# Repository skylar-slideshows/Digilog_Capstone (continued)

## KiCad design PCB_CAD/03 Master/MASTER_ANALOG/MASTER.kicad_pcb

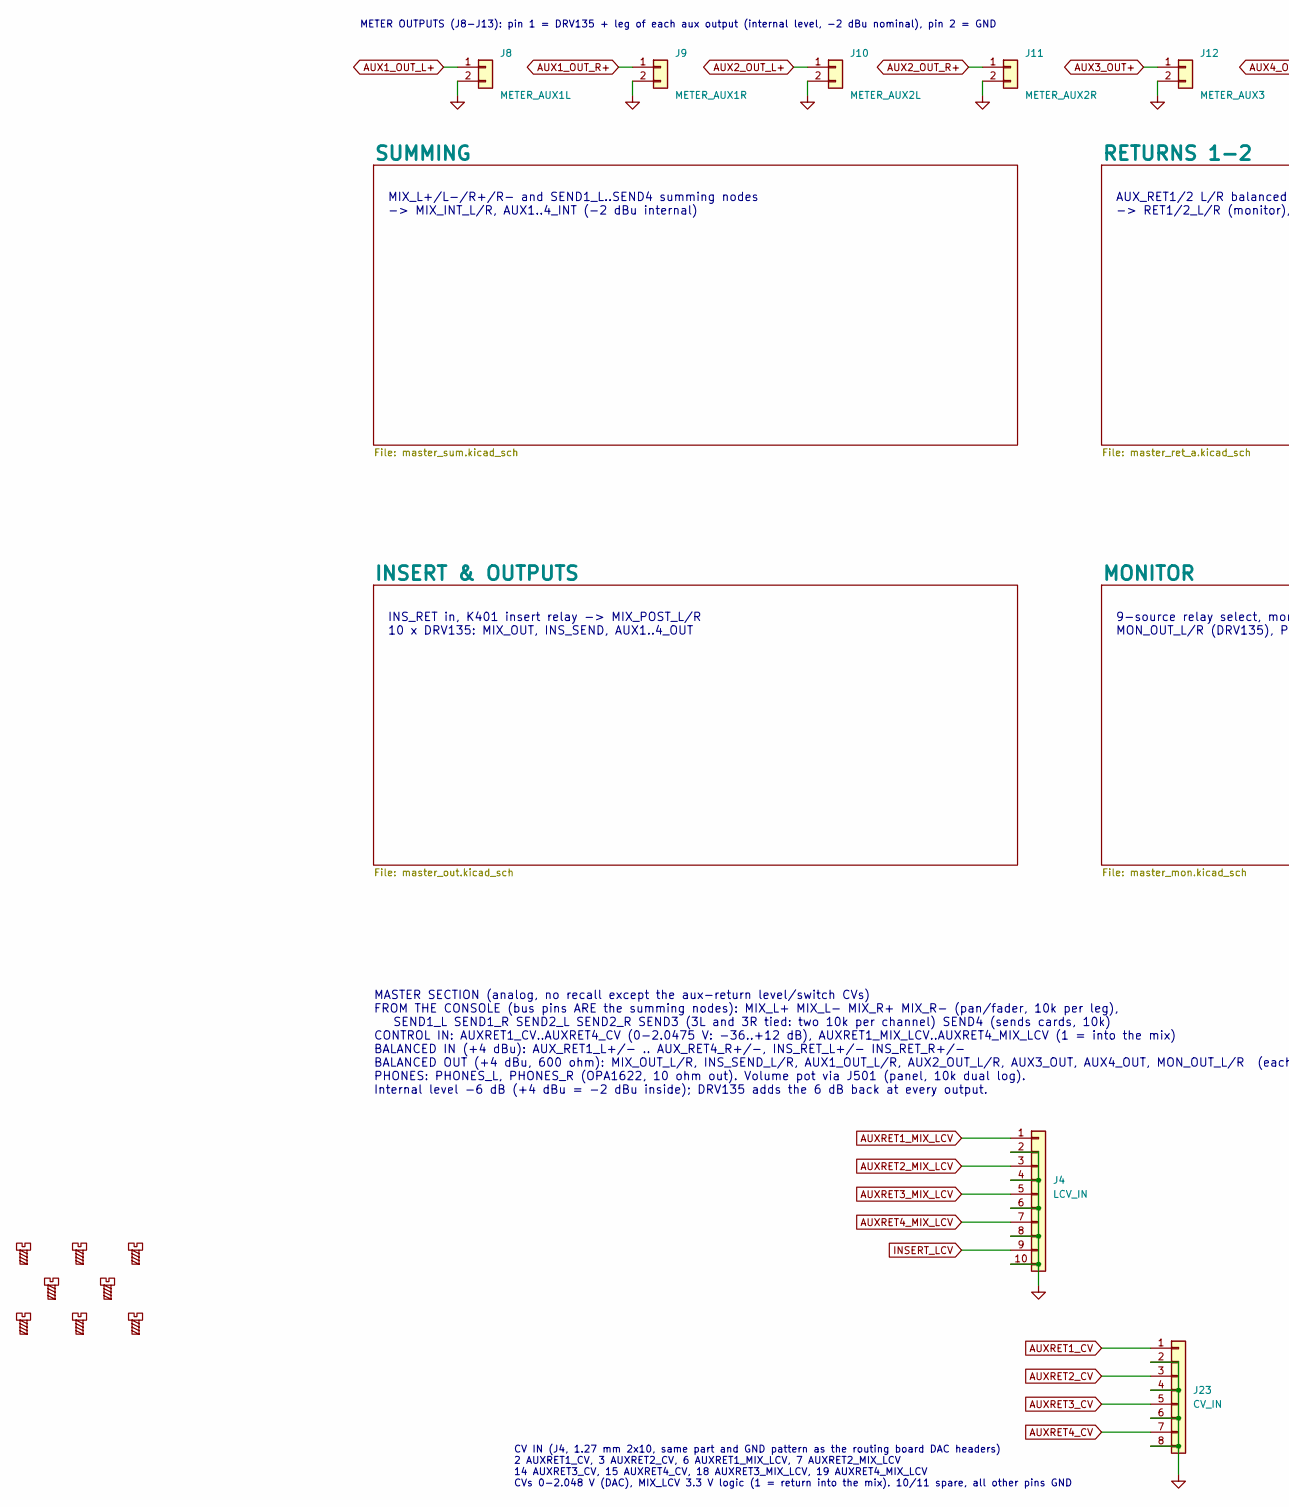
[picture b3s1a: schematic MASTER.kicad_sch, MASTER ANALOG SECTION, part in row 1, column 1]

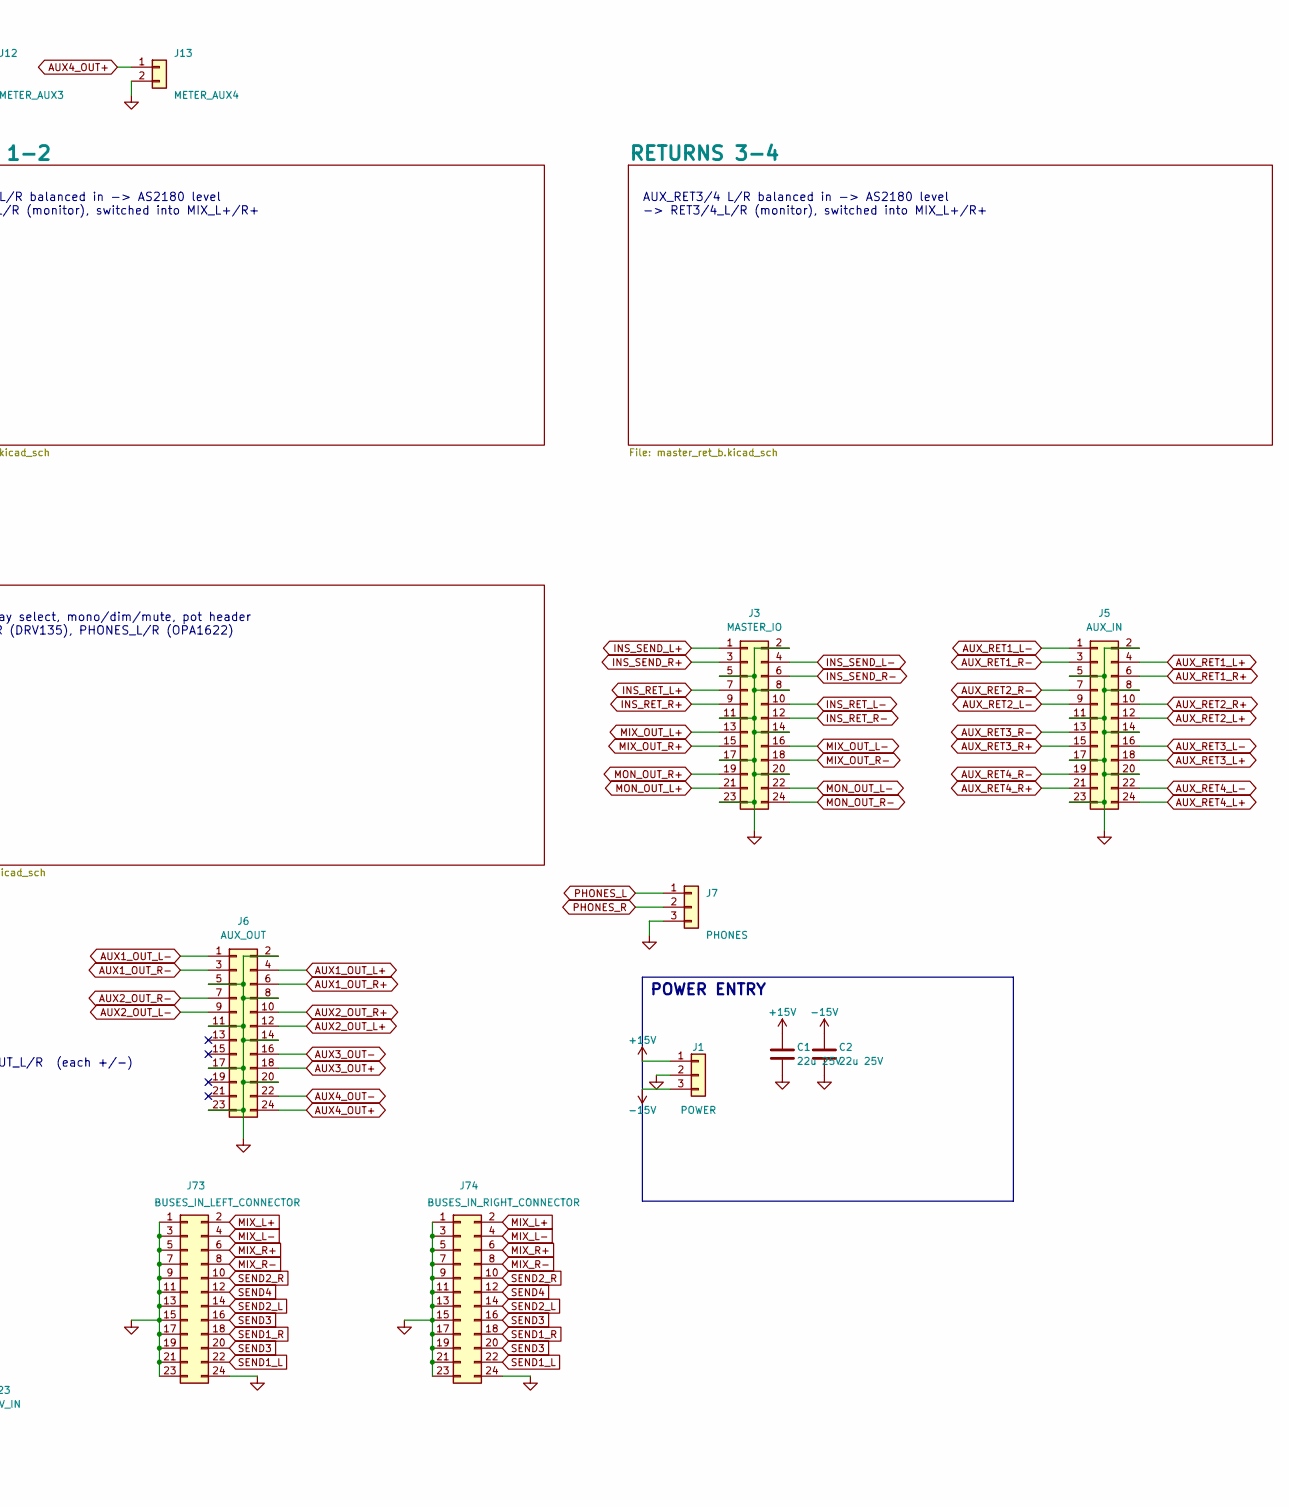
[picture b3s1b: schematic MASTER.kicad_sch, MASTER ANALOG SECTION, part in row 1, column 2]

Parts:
C1, C2: 22u 25V; C_1210_3225Metric; LCSC C21397
H1, H2, H3, H4, H5, H6, H7, H8: MountingScrew; MountingHole_3.2mm_M3; LCSC dnp
J1: POWER; Samtec_HPM-03-05-x-S_Straight_1x03_Pitch5.08mm; LCSC dnp
J3: MASTER_IO; IDC-Header_2x12_P2.54mm_Vertical; LCSC C53207829
J4: LCV_IN; PinHeader_1x10_P2.54mm_Vertical; LCSC dnp
J5: AUX_IN; IDC-Header_2x12_P2.54mm_Vertical; LCSC C53207829
J6: AUX_OUT; IDC-Header_2x12_P2.54mm_Vertical; LCSC C53207829
J7: PHONES; PinHeader_1x03_P2.54mm_Vertical; LCSC dnp
J8: METER_AUX1L; PinHeader_1x02_P2.54mm_Vertical; LCSC dnp
J9: METER_AUX1R; PinHeader_1x02_P2.54mm_Vertical; LCSC dnp
J10: METER_AUX2L; PinHeader_1x02_P2.54mm_Vertical; LCSC dnp
J11: METER_AUX2R; PinHeader_1x02_P2.54mm_Vertical; LCSC dnp
J12: METER_AUX3; PinHeader_1x02_P2.54mm_Vertical; LCSC dnp
J13: METER_AUX4; PinHeader_1x02_P2.54mm_Vertical; LCSC dnp
J23: CV_IN; PinHeader_1x08_P2.54mm_Vertical; LCSC dnp
J73: BUSES_IN_LEFT_CONNECTOR; IDC-Header_2x12_P2.54mm_Vertical; LCSC C53207829
J74: BUSES_IN_RIGHT_CONNECTOR; IDC-Header_2x12_P2.54mm_Vertical; LCSC C53207829

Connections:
+15V: C1.1, J1.1; also elsewhere on the board
-15V: C2.1, J1.3; also elsewhere on the board
AUX1_OUT_L+: J6.4, J8.1; also elsewhere on the board
AUX1_OUT_L-: J6.1; also elsewhere on the board
AUX1_OUT_R+: J6.6, J9.1; also elsewhere on the board
AUX1_OUT_R-: J6.3; also elsewhere on the board
AUX2_OUT_L+: J6.12, J10.1; also elsewhere on the board
AUX2_OUT_L-: J6.9; also elsewhere on the board
AUX2_OUT_R+: J6.10, J11.1; also elsewhere on the board
AUX2_OUT_R-: J6.7; also elsewhere on the board
AUX3_OUT+: J6.18, J12.1; also elsewhere on the board
AUX3_OUT-: J6.16; also elsewhere on the board
AUX4_OUT+: J6.24, J13.1; also elsewhere on the board
AUX4_OUT-: J6.22; also elsewhere on the board
AUXRET1_CV: J23.1; also elsewhere on the board
AUXRET1_MIX_LCV: J4.1; also elsewhere on the board
AUXRET2_CV: J23.3; also elsewhere on the board
AUXRET2_MIX_LCV: J4.3; also elsewhere on the board
AUXRET3_CV: J23.5; also elsewhere on the board
AUXRET3_MIX_LCV: J4.5; also elsewhere on the board
AUXRET4_CV: J23.7; also elsewhere on the board
AUXRET4_MIX_LCV: J4.7; also elsewhere on the board
AUX_RET1_L+: J5.4; also elsewhere on the board
AUX_RET1_L-: J5.1; also elsewhere on the board
AUX_RET1_R+: J5.6; also elsewhere on the board
AUX_RET1_R-: J5.3; also elsewhere on the board
AUX_RET2_L+: J5.12; also elsewhere on the board
AUX_RET2_L-: J5.9; also elsewhere on the board
AUX_RET2_R+: J5.10; also elsewhere on the board
AUX_RET2_R-: J5.7; also elsewhere on the board
AUX_RET3_L+: J5.18; also elsewhere on the board
AUX_RET3_L-: J5.16; also elsewhere on the board
AUX_RET3_R+: J5.15; also elsewhere on the board
AUX_RET3_R-: J5.13; also elsewhere on the board
AUX_RET4_L+: J5.24; also elsewhere on the board
AUX_RET4_L-: J5.22; also elsewhere on the board
AUX_RET4_R+: J5.21; also elsewhere on the board
AUX_RET4_R-: J5.19; also elsewhere on the board
GND: C1.2, C2.2, J1.2, J3.2, J3.5, J3.8, J3.11, J3.14, J3.17, J3.20, J3.23, J4.2, J4.4, J4.6, J4.8, J4.10, J5.2, J5.5, J5.8, J5.11, J5.14, J5.17, J5.20, J5.23, J6.2, J6.5, J6.8, J6.11, J6.14, J6.17, J6.20, J6.23, J7.3, J8.2, J9.2, J10.2, J11.2, J12.2, J13.2, J23.2, J23.4, J23.6, J23.8, J73.1, J73.3, J73.5, J73.7, J73.9, J73.11, J73.13, J73.15, J73.17, J73.19, J73.21, J73.23, J73.24, J74.1, J74.3, J74.5, J74.7, J74.9, J74.11, J74.13, J74.15, J74.17, J74.19, J74.21, J74.23, J74.24; also elsewhere on the board
INSERT_LCV: J4.9; also elsewhere on the board
INS_RET_L+: J3.7; also elsewhere on the board
INS_RET_L-: J3.10; also elsewhere on the board
INS_RET_R+: J3.9; also elsewhere on the board
INS_RET_R-: J3.12; also elsewhere on the board
INS_SEND_L+: J3.1; also elsewhere on the board
INS_SEND_L-: J3.4; also elsewhere on the board
INS_SEND_R+: J3.3; also elsewhere on the board
INS_SEND_R-: J3.6; also elsewhere on the board
MIX_L+: J73.2, J74.2; also elsewhere on the board
MIX_L-: J73.4, J74.4; also elsewhere on the board
MIX_OUT_L+: J3.13; also elsewhere on the board
MIX_OUT_L-: J3.16; also elsewhere on the board
MIX_OUT_R+: J3.15; also elsewhere on the board
MIX_OUT_R-: J3.18; also elsewhere on the board
MIX_R+: J73.6, J74.6; also elsewhere on the board
MIX_R-: J73.8, J74.8; also elsewhere on the board
MON_OUT_L+: J3.21; also elsewhere on the board
MON_OUT_L-: J3.22; also elsewhere on the board
MON_OUT_R+: J3.19; also elsewhere on the board
MON_OUT_R-: J3.24; also elsewhere on the board
PHONES_L: J7.1; also elsewhere on the board
PHONES_R: J7.2; also elsewhere on the board
SEND1_L: J73.22, J74.22; also elsewhere on the board
SEND1_R: J73.18, J74.18; also elsewhere on the board
SEND2_L: J73.14, J74.14; also elsewhere on the board
SEND2_R: J73.10, J74.10; also elsewhere on the board
SEND3: J73.16, J73.20, J74.16, J74.20; also elsewhere on the board
SEND4: J73.12, J74.12; also elsewhere on the board

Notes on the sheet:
MASTER SECTION (analog, no recall except the aux-return level/switch CVs) FROM THE CONSOLE (bus pins ARE the summing nodes): MIX_L+ MIX_L- MIX_R+ MIX_R- (pan/fader, 10k per leg), SEND1_L SEND1_R SEND2_L SEND2_R SEND3 (3L and 3R tied: two 10k per channel) SEND4 (sends cards, 10k) CONTROL IN: AUXRET1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
AUX_RET1/2 L/R balanced in -> AS2180 level -> RET1/2_L/R (monitor), switched into MIX_L+/R+
POWER ENTRY
CV IN (J4, 1.27 mm 2x10, same part and GND pattern as the routing board DAC headers) 2 AUXRET1_CV, 3 AUXRET2_CV, 6 AUXRET1_MIX_LCV, 7 AUXRET2_MIX_LCV 14 AUXRET3_CV, 15 AUXRET4_CV, 18 AUXRET3_MIX_LCV, 19 AUXRET4_MIX_LCV CVs 0-2.048 V (DAC), MIX_LCV 3.3 V logic (1 = return into the mix). 10/11 spare,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
9-source relay select, mono/dim/mute, pot header MON_OUT_L/R (DRV135), PHONES_L/R (OPA1622)
METER OUTPUTS (J8-J13): pin 1 = DRV135 + leg of each aux output (internal level, -2 dBu nominal), pin 2 = GND
AUX_RET3/4 L/R balanced in -> AS2180 level -> RET3/4_L/R (monitor), switched into MIX_L+/R+
INS_RET in, K401 insert relay -> MIX_POST_L/R 10 x DRV135: MIX_OUT, INS_SEND, AUX1..4_OUT
MIX_L+/L-/R+/R- and SEND1_L..SEND4 summing nodes -> MIX_INT_L/R, AUX1..4_INT (-2 dBu internal)

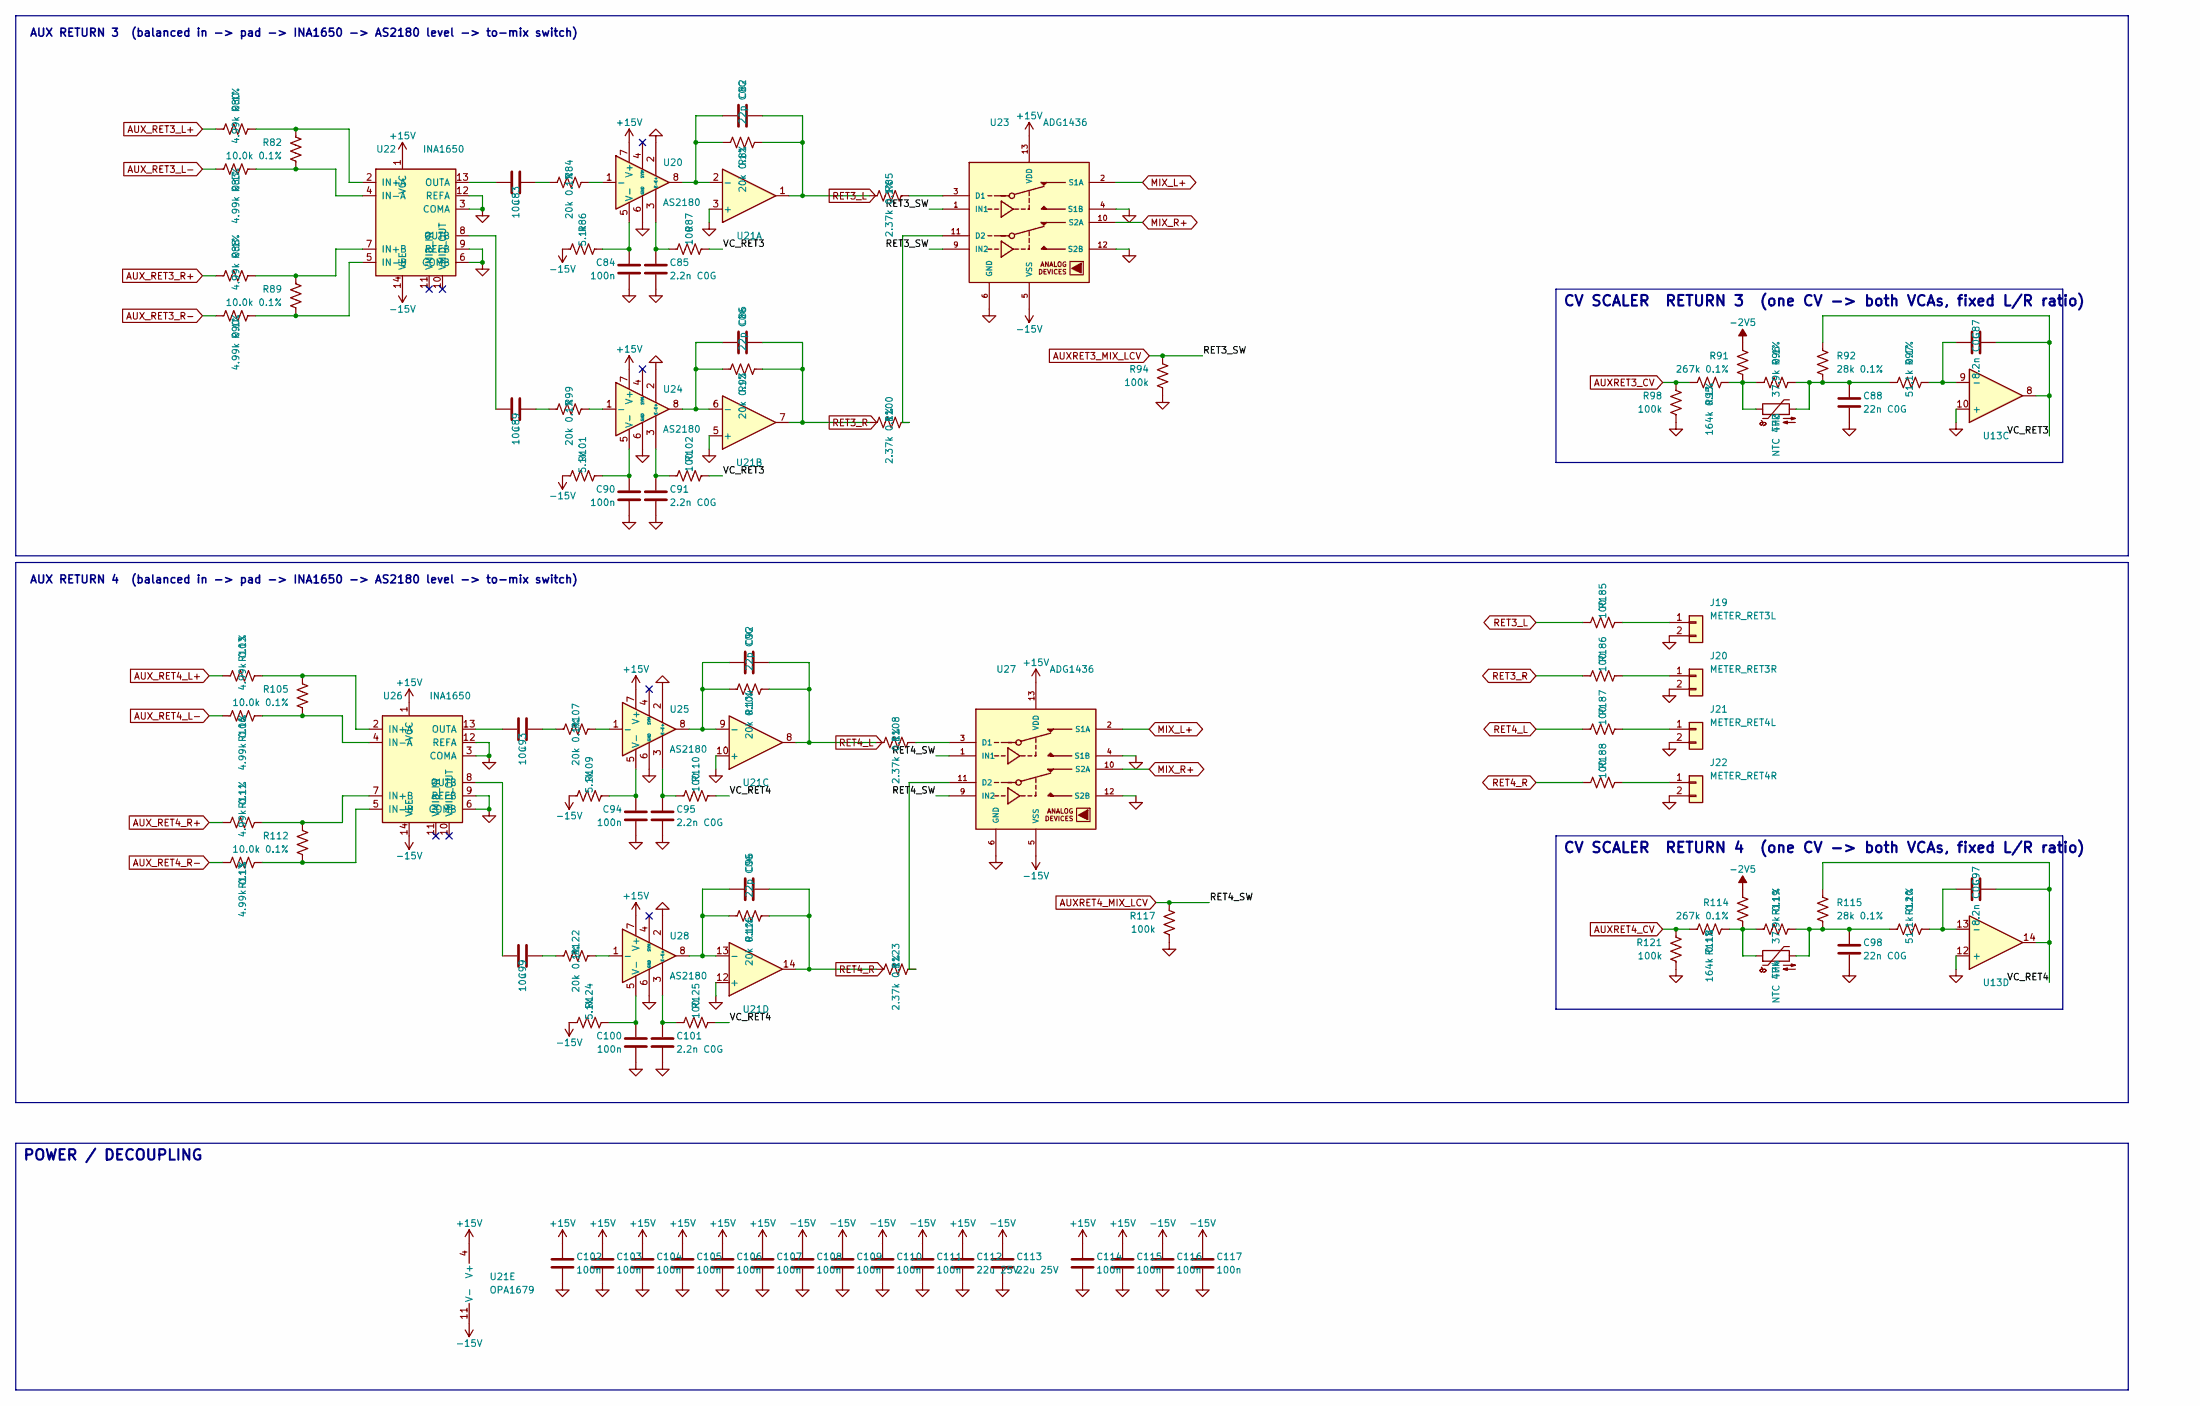
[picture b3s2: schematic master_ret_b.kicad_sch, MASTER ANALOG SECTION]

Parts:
C82, C86, C92, C96: 22p C0G; C_0603_1608Metric; LCSC C105620
C83, C89, C93, C99: 10u; CP_Elec_6.3x5.4_Nichicon; LCSC C340735
C84, C90, C94, C100, C102, C103, C104, C105, C106, C107, C108, C109, C110, C111, C114, C115, C116, C117: 100n; C_0603_1608Metric; LCSC C1590
C85, C91, C95, C101: 2.2n C0G; C_0603_1608Metric; LCSC C107043
C87, C97: 8.2n C0G; C_0805_2012Metric; LCSC C296107
C88, C98: 22n C0G; C_1206_3216Metric; LCSC C105982
C112, C113: 22u 25V; C_1210_3225Metric; LCSC C21397
J19: METER_RET3L; PinHeader_1x02_P2.54mm_Vertical; LCSC dnp
J20: METER_RET3R; PinHeader_1x02_P2.54mm_Vertical; LCSC dnp
J21: METER_RET4L; PinHeader_1x02_P2.54mm_Vertical; LCSC dnp
J22: METER_RET4R; PinHeader_1x02_P2.54mm_Vertical; LCSC dnp
R80, R83, R88, R90, R103, R106, R111, R113: 4.99k 0.1%; R_0603_1608Metric; LCSC C190614
R81, R84, R93, R99, R104, R107, R116, R122: 20k 0.1%; R_0603_1608Metric; LCSC C190611
R82, R89, R105, R112: 10.0k 0.1%; R_0603_1608Metric; LCSC C95204
R85, R100, R108, R123: 2.37k 0.1%; R_0603_1608Metric; LCSC C50670507
R86, R101, R109, R124: 5.1k; R_0603_1608Metric; LCSC C122969
R87, R102, R110, R125, R185, R186, R187, R188: 100; R_0603_1608Metric; LCSC C122970
R91, R114: 267k 0.1%; R_0603_1608Metric; LCSC C861785
R92, R115: 28k 0.1%; R_0603_1608Metric; LCSC C705756
R94, R98, R117, R121: 100k; R_0603_1608Metric; LCSC C122538
R95, R118: 164k 0.1%; R_0805_2012Metric; LCSC C865214
R96, R119: 37.9k 0.1%; R_0603_1608Metric; LCSC C861362
R97, R120: 51.1k 0.1%; R_0603_1608Metric; LCSC C491138
TH3, TH4: NTC 47k; R_Axial_DIN0207_L6.3mm_D2.5mm_P2.54mm_Vertical; LCSC dnp
U13: OPA4197; SOIC-14_3.9x8.7mm_P1.27mm; LCSC C2058532
U20, U24, U25, U28: AS2180; PinSocket_1x08_P2.54mm_Vertical; LCSC dnp
U21: OPA1679; TSSOP-14_4.4x5mm_P0.65mm; LCSC C2057264
U22, U26: INA1650; TSSOP-14_4.4x5mm_P0.65mm; LCSC C553130
U23, U27: ADG1436; TSSOP-16_4.4x5mm_P0.65mm; LCSC C408899

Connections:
+15V: C102.1, C103.1, C104.1, C105.1, C106.1, C107.1, C112.1, C114.1, C115.1, U20.7 (V+), U21.4 (V+), U22.1 (VCC), U23.13 (VDD), U24.7 (V+), U25.7 (V+), U26.1 (VCC), U27.13 (VDD), U28.7 (V+); also elsewhere on the board
-2V5: R91.1, R114.1; also elsewhere on the board
-15V: C108.1, C109.1, C110.1, C111.1, C113.1, C116.1, C117.1, R86.1, R101.1, R109.1, R124.1, U21.11 (V-), U22.14 (VEE), U23.5 (VSS), U26.14 (VEE), U27.5 (VSS); also elsewhere on the board
/RETURNS 3-4/VC_RET3: C87.2, R87.2, R92.1, R102.2, U13.8
/RETURNS 3-4/VC_RET4: C97.2, R110.2, R115.1, R125.2, U13.14
AUXRET3_CV: R95.1, R98.1; also elsewhere on the board
AUXRET3_MIX_LCV: R94.1, U23.1 (IN1), U23.9 (IN2); also elsewhere on the board
AUXRET4_CV: R118.1, R121.1; also elsewhere on the board
AUXRET4_MIX_LCV: R117.1, U27.1 (IN1), U27.9 (IN2); also elsewhere on the board
AUX_RET3_L+: R80.1; also elsewhere on the board
AUX_RET3_L-: R83.1; also elsewhere on the board
AUX_RET3_R+: R88.1; also elsewhere on the board
AUX_RET3_R-: R90.1; also elsewhere on the board
AUX_RET4_L+: R103.1; also elsewhere on the board
AUX_RET4_L-: R106.1; also elsewhere on the board
AUX_RET4_R+: R111.1; also elsewhere on the board
AUX_RET4_R-: R113.1; also elsewhere on the board
GND: C84.2, C85.2, C88.2, C90.2, C91.2, C94.2, C95.2, C98.2, C100.2, C101.2, C102.2, C103.2, C104.2, C105.2, C106.2, C107.2, C108.2, C109.2, C110.2, C111.2, C112.2, C113.2, C114.2, C115.2, C116.2, C117.2, J19.2, J20.2, J21.2, J22.2, R94.2, R98.2, R117.2, R121.2, U13.10 (+), U13.12 (+), U20.2 (E+), U20.6 (GND), U21.3 (+), U21.5 (+), U21.10 (+), U21.12 (+), U22.3 (COMA), U22.6 (COMB), U22.9 (REFB), U22.12 (REFA), U23.4 (S1B), U23.6 (GND), U23.12 (S2B), U24.2 (E+), U24.6 (GND), U25.2 (E+), U25.6 (GND), U26.3 (COMA), U26.6 (COMB), U26.9 (REFB), U26.12 (REFA), U27.4 (S1B), U27.6 (GND), U27.12 (S2B), U28.2 (E+), U28.6 (GND); also elsewhere on the board
MIX_L+: U23.2 (S1A), U27.2 (S1A); also elsewhere on the board
MIX_R+: U23.10 (S2A), U27.10 (S2A); also elsewhere on the board
unnamed: C83.2, R84.1
unnamed: C88.1, R92.2, R96.2, R97.1, TH3.2
unnamed: C89.2, R99.1
unnamed: C93.2, R107.1
unnamed: C98.1, R115.2, R119.2, R120.1, TH4.2
unnamed: C99.2, R122.1
unnamed: J19.1, R185.2
unnamed: J20.1, R186.2
unnamed: J21.1, R187.2
unnamed: J22.1, R188.2
unnamed: R91.2, R95.2, R96.1, TH3.1
unnamed: R114.2, R118.2, R119.1, TH4.1
unnamed: C87.1, R97.2, U13.9 (-)
unnamed: C97.1, R120.2, U13.13 (-)
unnamed: R84.2, U20.1 (-)
unnamed: C85.1, R87.1, U20.3 (E-)
unnamed: C84.1, R86.2, U20.5 (V-)
unnamed: C82.1, R81.1, U20.8, U21.2 (-)
unnamed: C86.1, R93.1, U21.6 (-), U24.8
unnamed: C92.1, R104.1, U21.9 (-), U25.8
unnamed: C96.1, R116.1, U21.13 (-), U28.8
unnamed: R80.2, R82.1, U22.2 (IN+A)
unnamed: R88.2, R89.1, U22.7 (IN+B)
unnamed: R82.2, R83.2, U22.4 (IN-A)
unnamed: R89.2, R90.2, U22.5 (IN-B)
unnamed: C83.1, U22.13 (OUTA)
unnamed: C89.1, U22.8 (OUTB)
unnamed: R85.2, U23.3 (D1)
unnamed: R100.2, U23.11 (D2)
unnamed: R99.2, U24.1 (-)
unnamed: C91.1, R102.1, U24.3 (E-)
unnamed: C90.1, R101.2, U24.5 (V-)
unnamed: R107.2, U25.1 (-)
unnamed: C95.1, R110.1, U25.3 (E-)
unnamed: C94.1, R109.2, U25.5 (V-)
unnamed: R103.2, R105.1, U26.2 (IN+A)
unnamed: R111.2, R112.1, U26.7 (IN+B)
unnamed: R105.2, R106.2, U26.4 (IN-A)
unnamed: R112.2, R113.2, U26.5 (IN-B)
unnamed: C93.1, U26.13 (OUTA)
unnamed: C99.1, U26.8 (OUTB)
unnamed: R108.2, U27.3 (D1)
unnamed: R123.2, U27.11 (D2)
unnamed: R122.2, U28.1 (-)
unnamed: C101.1, R125.1, U28.3 (E-)
unnamed: C100.1, R124.2, U28.5 (V-)
RET3_L: C82.2, R81.2, R85.1, R185.1, U21.1; also elsewhere on the board
RET3_R: C86.2, R93.2, R100.1, R186.1, U21.7; also elsewhere on the board
RET4_L: C92.2, R104.2, R108.1, R187.1, U21.8; also elsewhere on the board
RET4_R: C96.2, R116.2, R123.1, R188.1, U21.14; also elsewhere on the board

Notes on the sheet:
POWER / DECOUPLING
AUX RETURN 4 (balanced in -> pad -> INA1650 -> AS2180 level -> to-mix switch)
CV SCALER RETURN 4 (one CV -> both VCAs, fixed L/R ratio)
AUX RETURN 3 (balanced in -> pad -> INA1650 -> AS2180 level -> to-mix switch)
CV SCALER RETURN 3 (one CV -> both VCAs, fixed L/R ratio)

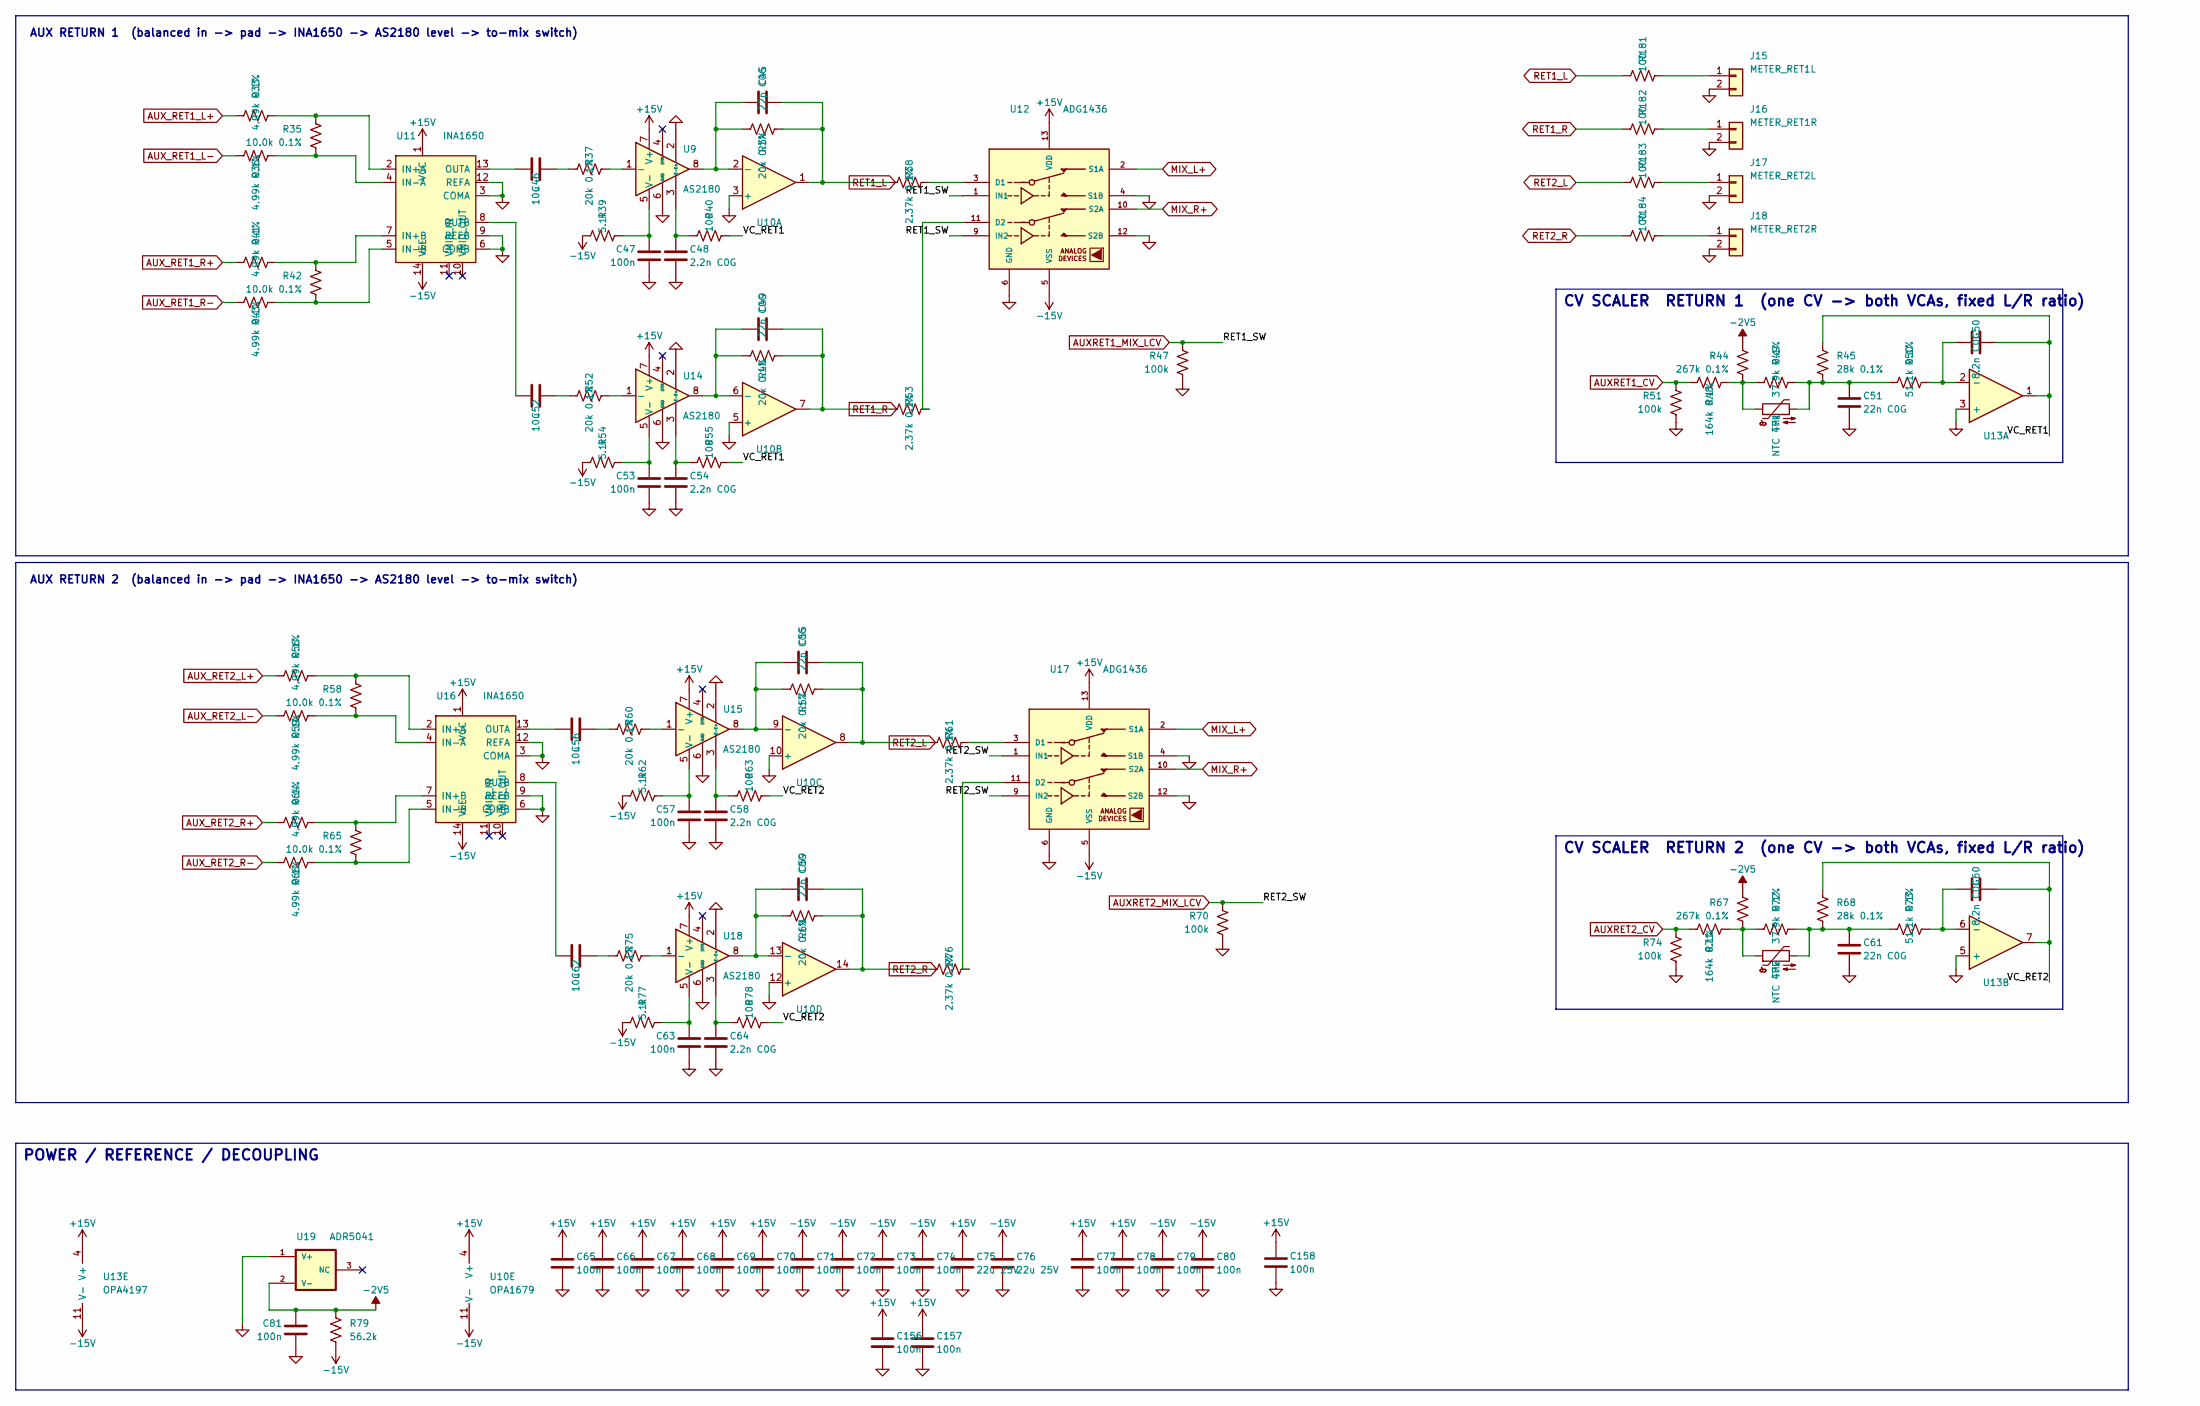
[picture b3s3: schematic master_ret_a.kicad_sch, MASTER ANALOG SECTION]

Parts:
C45, C49, C55, C59: 22p C0G; C_0603_1608Metric; LCSC C105620
C46, C52, C56, C62: 10u; CP_Elec_6.3x5.4_Nichicon; LCSC C340735
C47, C53, C57, C63, C65, C66, C67, C68, C69, C70, C71, C72, C73, C74, C77, C78, C79, C80, C81, C156, C157, C158: 100n; C_0603_1608Metric; LCSC C1590
C48, C54, C58, C64: 2.2n C0G; C_0603_1608Metric; LCSC C107043
C50, C60: 8.2n C0G; C_0805_2012Metric; LCSC C296107
C51, C61: 22n C0G; C_1206_3216Metric; LCSC C105982
C75, C76: 22u 25V; C_1210_3225Metric; LCSC C21397
J15: METER_RET1L; PinHeader_1x02_P2.54mm_Vertical; LCSC dnp
J16: METER_RET1R; PinHeader_1x02_P2.54mm_Vertical; LCSC dnp
J17: METER_RET2L; PinHeader_1x02_P2.54mm_Vertical; LCSC dnp
J18: METER_RET2R; PinHeader_1x02_P2.54mm_Vertical; LCSC dnp
R33, R36, R41, R43, R56, R59, R64, R66: 4.99k 0.1%; R_0603_1608Metric; LCSC C190614
R34, R37, R46, R52, R57, R60, R69, R75: 20k 0.1%; R_0603_1608Metric; LCSC C190611
R35, R42, R58, R65: 10.0k 0.1%; R_0603_1608Metric; LCSC C95204
R38, R53, R61, R76: 2.37k 0.1%; R_0603_1608Metric; LCSC C50670507
R39, R54, R62, R77: 5.1k; R_0603_1608Metric; LCSC C122969
R40, R55, R63, R78, R181, R182, R183, R184: 100; R_0603_1608Metric; LCSC C122970
R44, R67: 267k 0.1%; R_0603_1608Metric; LCSC C861785
R45, R68: 28k 0.1%; R_0603_1608Metric; LCSC C705756
R47, R51, R70, R74: 100k; R_0603_1608Metric; LCSC C122538
R48, R71: 164k 0.1%; R_0805_2012Metric; LCSC C865214
R49, R72: 37.9k 0.1%; R_0603_1608Metric; LCSC C861362
R50, R73: 51.1k 0.1%; R_0603_1608Metric; LCSC C491138
R79: 56.2k; R_0603_1608Metric; LCSC C23080
TH1, TH2: NTC 47k; R_Axial_DIN0207_L6.3mm_D2.5mm_P2.54mm_Vertical; LCSC dnp
U9, U14, U15, U18: AS2180; PinSocket_1x08_P2.54mm_Vertical; LCSC dnp
U10: OPA1679; TSSOP-14_4.4x5mm_P0.65mm; LCSC C2057264
U11, U16: INA1650; TSSOP-14_4.4x5mm_P0.65mm; LCSC C553130
U12, U17: ADG1436; TSSOP-16_4.4x5mm_P0.65mm; LCSC C408899
U13: OPA4197; SOIC-14_3.9x8.7mm_P1.27mm; LCSC C2058532
U19: ADR5041; SOT-23; LCSC C2686108

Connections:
+15V: C65.1, C66.1, C67.1, C68.1, C69.1, C70.1, C75.1, C77.1, C78.1, C156.1, C157.1, C158.1, U9.7 (V+), U10.4 (V+), U11.1 (VCC), U12.13 (VDD), U13.4 (V+), U14.7 (V+), U15.7 (V+), U16.1 (VCC), U17.13 (VDD), U18.7 (V+); also elsewhere on the board
-2V5: C81.1, R44.1, R67.1, R79.1, U19.2 (V-); also elsewhere on the board
-15V: C71.1, C72.1, C73.1, C74.1, C76.1, C79.1, C80.1, R39.1, R54.1, R62.1, R77.1, R79.2, U10.11 (V-), U11.14 (VEE), U12.5 (VSS), U13.11 (V-), U16.14 (VEE), U17.5 (VSS); also elsewhere on the board
/RETURNS 1-2/VC_RET1: C50.2, R40.2, R45.1, R55.2, U13.1
/RETURNS 1-2/VC_RET2: C60.2, R63.2, R68.1, R78.2, U13.7
AUXRET1_CV: R48.1, R51.1; also elsewhere on the board
AUXRET1_MIX_LCV: R47.1, U12.1 (IN1), U12.9 (IN2); also elsewhere on the board
AUXRET2_CV: R71.1, R74.1; also elsewhere on the board
AUXRET2_MIX_LCV: R70.1, U17.1 (IN1), U17.9 (IN2); also elsewhere on the board
AUX_RET1_L+: R33.1; also elsewhere on the board
AUX_RET1_L-: R36.1; also elsewhere on the board
AUX_RET1_R+: R41.1; also elsewhere on the board
AUX_RET1_R-: R43.1; also elsewhere on the board
AUX_RET2_L+: R56.1; also elsewhere on the board
AUX_RET2_L-: R59.1; also elsewhere on the board
AUX_RET2_R+: R64.1; also elsewhere on the board
AUX_RET2_R-: R66.1; also elsewhere on the board
GND: C47.2, C48.2, C51.2, C53.2, C54.2, C57.2, C58.2, C61.2, C63.2, C64.2, C65.2, C66.2, C67.2, C68.2, C69.2, C70.2, C71.2, C72.2, C73.2, C74.2, C75.2, C76.2, C77.2, C78.2, C79.2, C80.2, C81.2, C156.2, C157.2, C158.2, J15.2, J16.2, J17.2, J18.2, R47.2, R51.2, R70.2, R74.2, U9.2 (E+), U9.6 (GND), U10.3 (+), U10.5 (+), U10.10 (+), U10.12 (+), U11.3 (COMA), U11.6 (COMB), U11.9 (REFB), U11.12 (REFA), U12.4 (S1B), U12.6 (GND), U12.12 (S2B), U13.3 (+), U13.5 (+), U14.2 (E+), U14.6 (GND), U15.2 (E+), U15.6 (GND), U16.3 (COMA), U16.6 (COMB), U16.9 (REFB), U16.12 (REFA), U17.4 (S1B), U17.6 (GND), U17.12 (S2B), U18.2 (E+), U18.6 (GND), U19.1 (V+); also elsewhere on the board
MIX_L+: U12.2 (S1A), U17.2 (S1A); also elsewhere on the board
MIX_R+: U12.10 (S2A), U17.10 (S2A); also elsewhere on the board
unnamed: C46.2, R37.1
unnamed: C51.1, R45.2, R49.2, R50.1, TH1.2
unnamed: C52.2, R52.1
unnamed: C56.2, R60.1
unnamed: C61.1, R68.2, R72.2, R73.1, TH2.2
unnamed: C62.2, R75.1
unnamed: J15.1, R181.2
unnamed: J16.1, R182.2
unnamed: J17.1, R183.2
unnamed: J18.1, R184.2
unnamed: R44.2, R48.2, R49.1, TH1.1
unnamed: R67.2, R71.2, R72.1, TH2.1
unnamed: R37.2, U9.1 (-)
unnamed: C48.1, R40.1, U9.3 (E-)
unnamed: C47.1, R39.2, U9.5 (V-)
unnamed: C45.1, R34.1, U9.8, U10.2 (-)
unnamed: C49.1, R46.1, U10.6 (-), U14.8
unnamed: C55.1, R57.1, U10.9 (-), U15.8
unnamed: C59.1, R69.1, U10.13 (-), U18.8
unnamed: R33.2, R35.1, U11.2 (IN+A)
unnamed: R41.2, R42.1, U11.7 (IN+B)
unnamed: R35.2, R36.2, U11.4 (IN-A)
unnamed: R42.2, R43.2, U11.5 (IN-B)
unnamed: C46.1, U11.13 (OUTA)
unnamed: C52.1, U11.8 (OUTB)
unnamed: R38.2, U12.3 (D1)
unnamed: R53.2, U12.11 (D2)
unnamed: C50.1, R50.2, U13.2 (-)
unnamed: C60.1, R73.2, U13.6 (-)
unnamed: R52.2, U14.1 (-)
unnamed: C54.1, R55.1, U14.3 (E-)
unnamed: C53.1, R54.2, U14.5 (V-)
unnamed: R60.2, U15.1 (-)
unnamed: C58.1, R63.1, U15.3 (E-)
unnamed: C57.1, R62.2, U15.5 (V-)
unnamed: R56.2, R58.1, U16.2 (IN+A)
unnamed: R64.2, R65.1, U16.7 (IN+B)
unnamed: R58.2, R59.2, U16.4 (IN-A)
unnamed: R65.2, R66.2, U16.5 (IN-B)
unnamed: C56.1, U16.13 (OUTA)
unnamed: C62.1, U16.8 (OUTB)
unnamed: R61.2, U17.3 (D1)
unnamed: R76.2, U17.11 (D2)
unnamed: R75.2, U18.1 (-)
unnamed: C64.1, R78.1, U18.3 (E-)
unnamed: C63.1, R77.2, U18.5 (V-)
RET1_L: C45.2, R34.2, R38.1, R181.1, U10.1; also elsewhere on the board
RET1_R: C49.2, R46.2, R53.1, R182.1, U10.7; also elsewhere on the board
RET2_L: C55.2, R57.2, R61.1, R183.1, U10.8; also elsewhere on the board
RET2_R: C59.2, R69.2, R76.1, R184.1, U10.14; also elsewhere on the board

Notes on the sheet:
AUX RETURN 1 (balanced in -> pad -> INA1650 -> AS2180 level -> to-mix switch)
AUX RETURN 2 (balanced in -> pad -> INA1650 -> AS2180 level -> to-mix switch)
POWER / REFERENCE / DECOUPLING
CV SCALER RETURN 1 (one CV -> both VCAs, fixed L/R ratio)
CV SCALER RETURN 2 (one CV -> both VCAs, fixed L/R ratio)
